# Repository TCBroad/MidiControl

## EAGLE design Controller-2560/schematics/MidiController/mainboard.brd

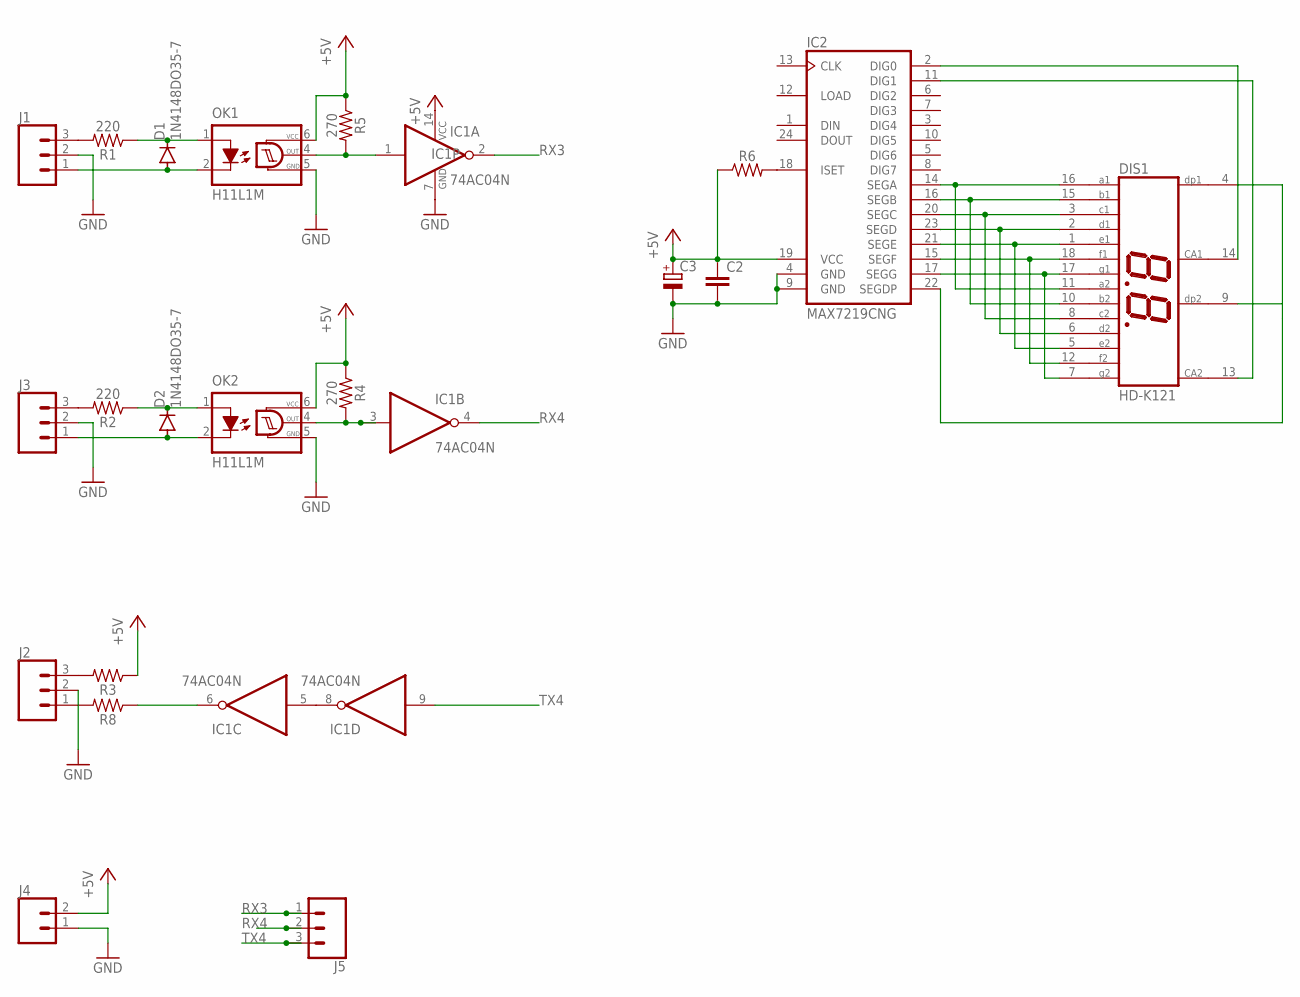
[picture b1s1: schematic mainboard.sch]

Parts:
C2: C-EU025-025X050; C025-025X050
C3: CPOL-EUE1.8-4; E1,8-4
D1, D2: 1N4148DO35-7; DO35-7
DIS1: HD-K121; HDSP-R
IC1: 74AC04N; DIL14
IC2: MAX7219CNG; DIL24-3
J1, J2, J3, J5: CONN_03; 1X03
J4: CONN_02; 1X02
OK1, OK2: H11L1M; DIL06
R1, R2: 220; AXIAL-0.3
R3, R6, R8: AXIAL-0.3
R4, R5: 270; AXIAL-0.3

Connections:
+5V: C2.1, C3.+, IC1.14 (VCC), IC2.19 (VCC), J4.2, OK1.6 (VCC), OK2.6 (VCC), R3.P$1 (1), R4.P$1 (1), R5.P$1 (1), R6.P$1 (1)
GND: C2.2, C3.-, IC1.7 (GND), IC2.4 (GND), IC2.9 (GND), J1.2, J2.2, J3.2, J4.1, OK1.5 (GND), OK2.5 (GND)
unnamed: IC1.5 (I), IC1.8 (O)
unnamed: J1.3, R1.P$2 (2)
unnamed: D1.A, J1.1, OK1.2 (C)
unnamed: D1.C, OK1.1 (A), R1.P$1 (1)
unnamed: J3.3, R2.P$2 (2)
unnamed: D2.A, J3.1, OK2.2 (C)
unnamed: D2.C, OK2.1 (A), R2.P$1 (1)
unnamed: IC1.1 (I), OK1.4 (OUT), R5.P$2 (2)
unnamed: IC1.3 (I), OK2.4 (OUT), R4.P$2 (2)
unnamed: J2.3, R3.P$2 (2)
unnamed: J2.1, R8.P$2 (2)
unnamed: IC1.6 (O), R8.P$1 (1)
unnamed: IC2.18 (ISET), R6.P$2 (2)
unnamed: DIS1.11 (A2), DIS1.16 (A1), IC2.14 (SEGA)
unnamed: DIS1.10 (B2), DIS1.15 (B1), IC2.16 (SEGB)
unnamed: DIS1.3 (C1), DIS1.8 (C2), IC2.20 (SEGC)
unnamed: DIS1.2 (D1), DIS1.6 (D2), IC2.23 (SEGD)
unnamed: DIS1.1 (E1), DIS1.5 (E2), IC2.21 (SEGE)
unnamed: DIS1.12 (F2), DIS1.18 (F1), IC2.15 (SEGF)
unnamed: DIS1.7 (G2), DIS1.17 (G1), IC2.17 (SEGG)
unnamed: DIS1.4 (DP1), DIS1.9 (DP2), IC2.22 (SEGDP)
unnamed: DIS1.14 (CA1), IC2.2 (DIG0)
unnamed: DIS1.13 (CA2), IC2.11 (DIG1)
RX3: IC1.2 (O), J5.1
RX4: IC1.4 (O), J5.2
TX4: IC1.9 (I), J5.3

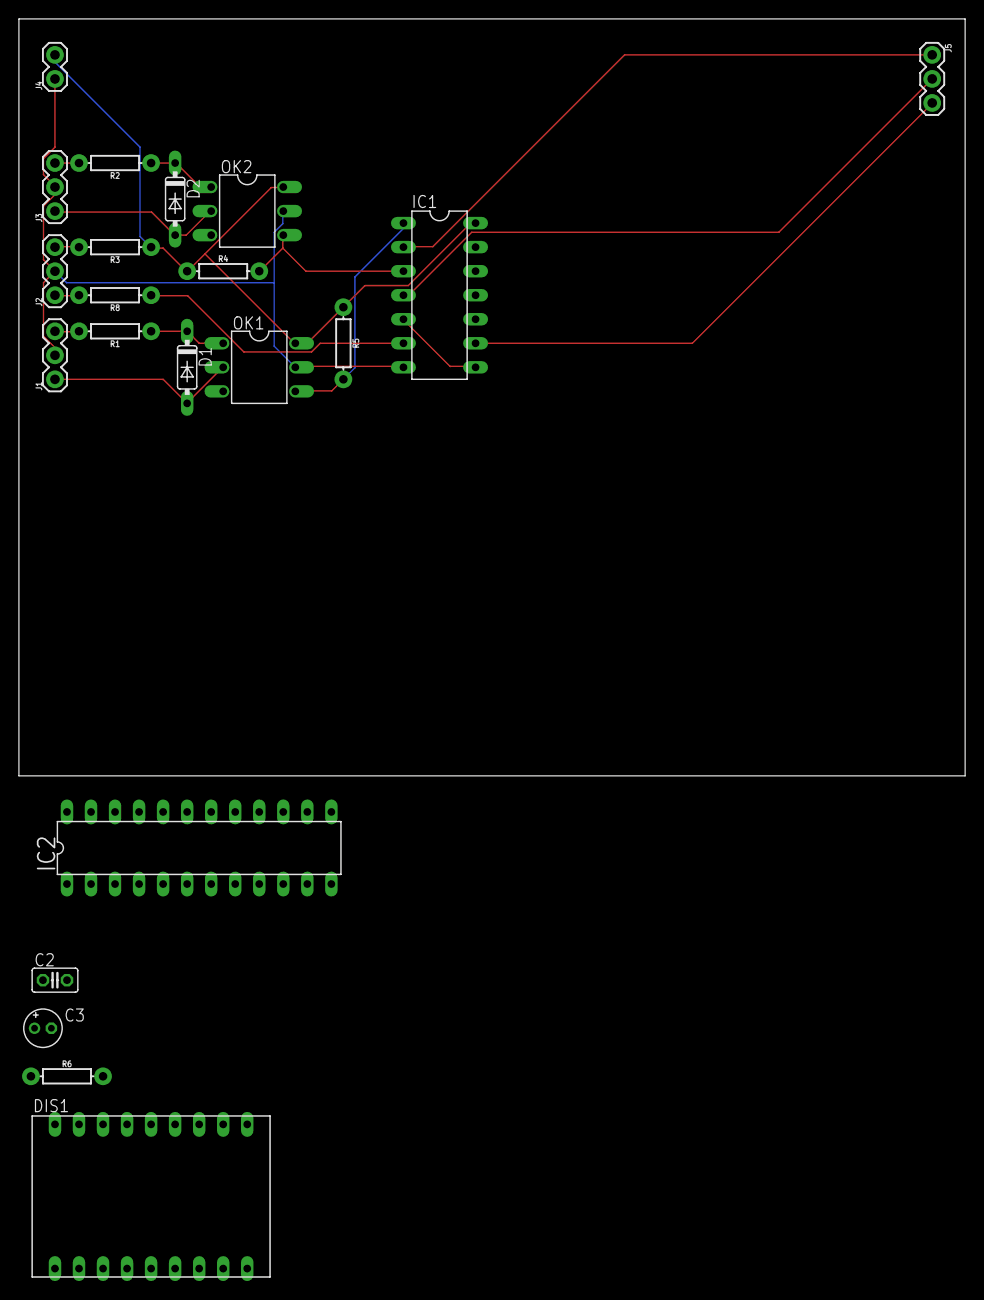
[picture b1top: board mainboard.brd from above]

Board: 2 copper layers, 100.0 x 80.0 mm, 21 parts (0 on the bottom side), 28 nets.

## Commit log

2018-10-09 Added existing code
2018-10-11 fixed non-preset selection added LEDs
2018-10-20 added schematic (WIP) changed serial port, refactoring
2018-10-21 Added scenes + status LED
2018-10-21 Handle scenes properly Keypad layout changed MIDI Merge works
2018-10-22 Added mute Refactoring Better led output
2018-10-22 Refactoring
2018-10-27 Updated schematic
2018-11-02 Added led display output
2018-11-02 added decimal point flash on midi input
2018-11-05 added sysex read + axe fx funcs
2018-11-06 bugfixes after testing with actual hardware
2018-11-08 Got fresh project working in clion
2018-11-09 Started pulling old code out into classes
2018-11-11 Added methods to header
2018-11-11 Added implementations of class
2018-11-13 Implemented various hal methods
2018-11-18 Refactoring, added tcl5947 support, removed String usage
2019-07-14 Implemented remaining methods, changed types - update to pio 4
2019-07-19 Big refactor, basically rewrite
2020-07-27 [hardware] Everything runs on SPI. Moved to stm32

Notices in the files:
parts and their libraries:
SparkFun-Connectors: Licensing: Creative Commons ShareAlike 4.0 International - https://creativecommons.org/licenses/by-sa/4.0
